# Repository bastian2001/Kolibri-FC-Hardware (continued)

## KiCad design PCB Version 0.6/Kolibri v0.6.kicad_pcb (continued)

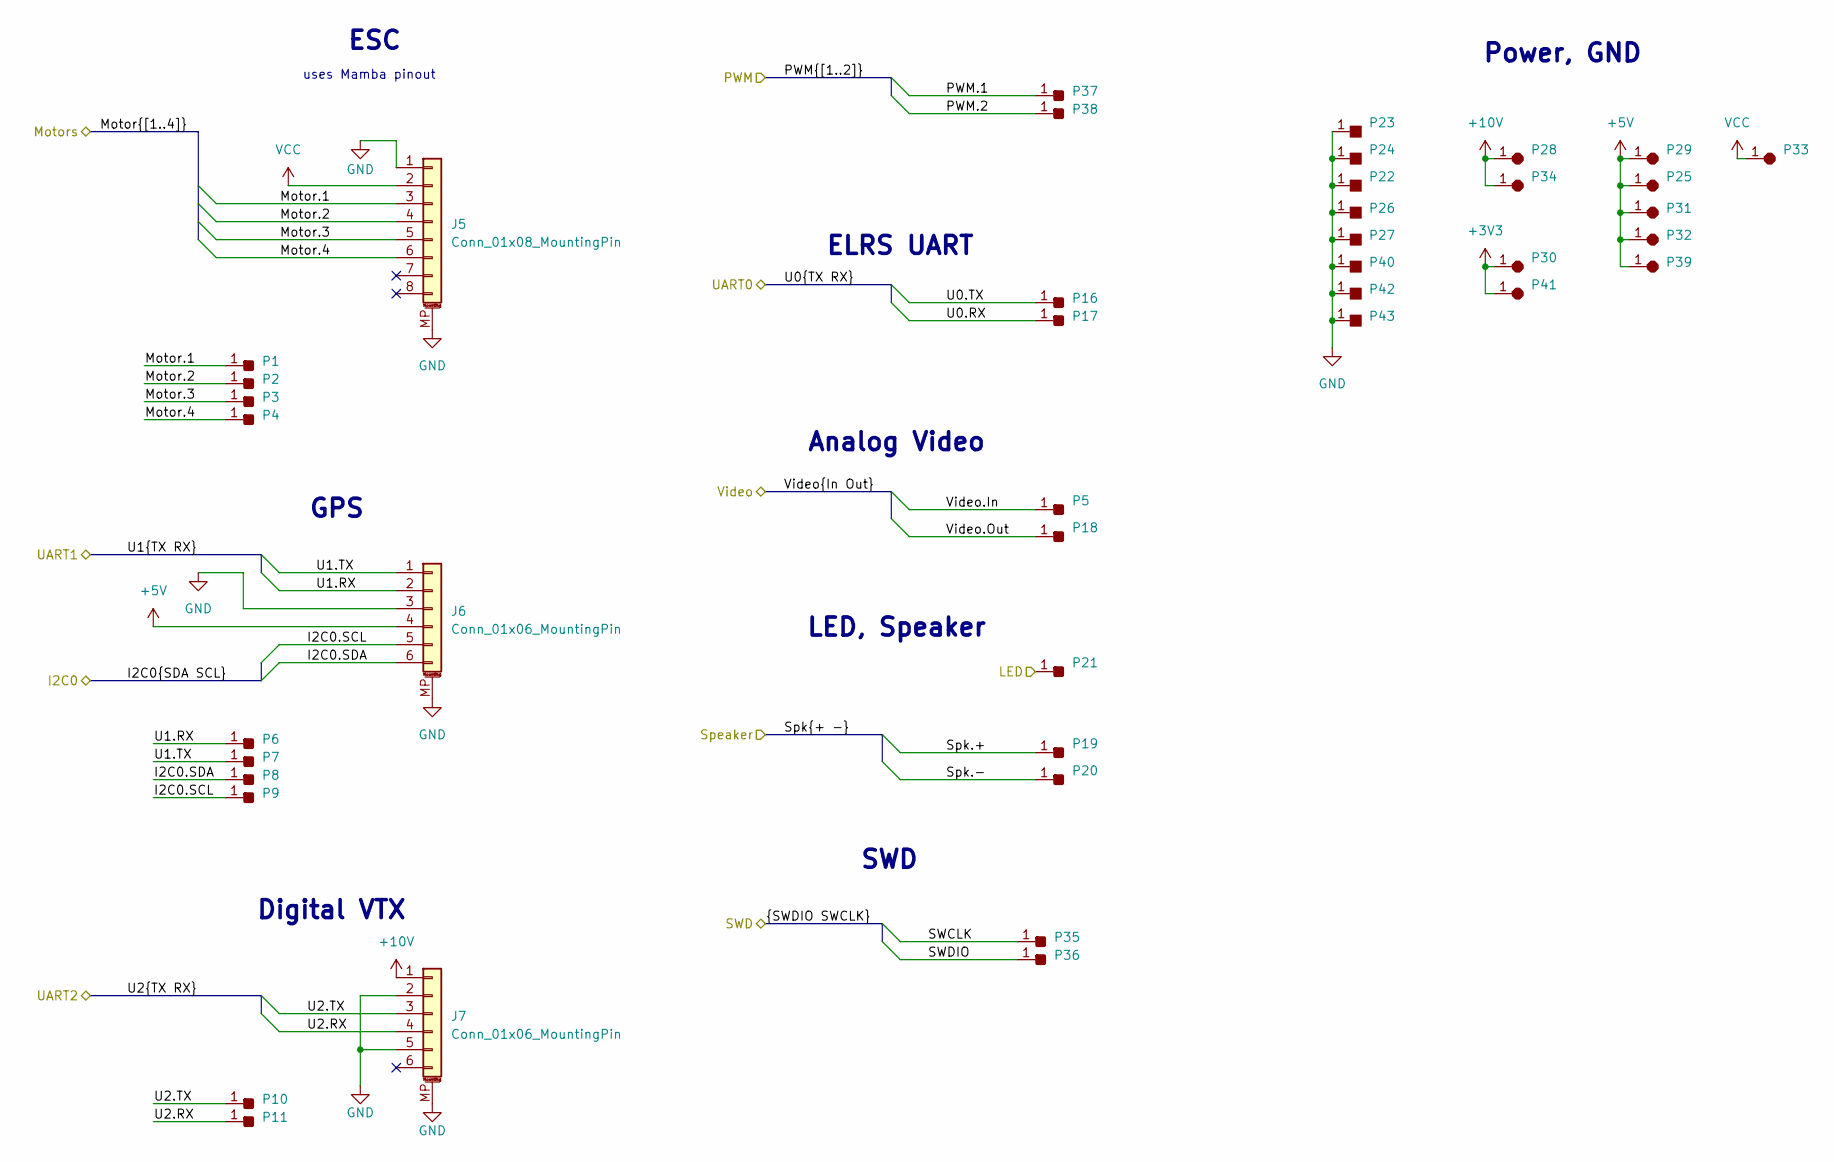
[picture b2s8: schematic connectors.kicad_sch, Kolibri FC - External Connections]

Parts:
J5: Conn_01x08_MountingPin; JST_SH_SM08B-SRSS-TB_1x08-1MP_P1.00mm_Horizontal
J6, J7: Conn_01x06_MountingPin; JST_SH_SM06B-SRSS-TB_1x06-1MP_P1.00mm_Horizontal
P1, P2, P3, P4, P5, P6, P7, P8, P9, P10, P11, P16, P17, P18, P19, P20, P21, P35, P36, P37, P38: Solder_Pad_rounded
P22, P23, P24, P26, P27, P40, P42, P43: Solder_Pad_rect
P25, P28, P29, P30, P31, P32, P33, P34, P39, P41: Solder_Pad_octa

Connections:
+3V3: P30.1, P41.1; also elsewhere on the board
+5V: J6.4, P25.1, P29.1, P31.1, P32.1, P39.1; also elsewhere on the board
+10V: J7.1, P28.1, P34.1; also elsewhere on the board
/Connectors/LED: P21.1; also elsewhere on the board
/I2C0.SCL: J6.5, P9.1; also elsewhere on the board
/I2C0.SDA: J6.6, P8.1; also elsewhere on the board
/Motor.1: J5.3, P1.1; also elsewhere on the board
/Motor.2: J5.4, P2.1; also elsewhere on the board
/Motor.3: J5.5, P3.1; also elsewhere on the board
/Motor.4: J5.6, P4.1; also elsewhere on the board
/PWM.1: P38.1; also elsewhere on the board
/PWM.2: P37.1; also elsewhere on the board
/SWCLK: P35.1; also elsewhere on the board
/SWDIO: P36.1; also elsewhere on the board
/Spk.+: P19.1; also elsewhere on the board
/Spk.-: P20.1; also elsewhere on the board
/U0.RX: P17.1; also elsewhere on the board
/U0.TX: P16.1; also elsewhere on the board
/U1.RX: J6.2, P6.1; also elsewhere on the board
/U1.TX: J6.1, P7.1; also elsewhere on the board
/U2.RX: J7.4, P11.1; also elsewhere on the board
/U2.TX: J7.3, P10.1; also elsewhere on the board
/Video.In: P5.1; also elsewhere on the board
/Video.Out: P18.1; also elsewhere on the board
GND: J5.1, J5.MP (MountPin), J6.3, J6.MP (MountPin), J7.2, J7.5, J7.MP (MountPin), P22.1, P23.1, P24.1, P26.1, P27.1, P40.1, P42.1, P43.1; also elsewhere on the board
VCC: J5.2, P33.1; also elsewhere on the board

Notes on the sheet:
Power, GND
GPS
LED, Speaker
SWD
Analog Video
ESC
uses Mamba pinout
Digital VTX
ELRS UART

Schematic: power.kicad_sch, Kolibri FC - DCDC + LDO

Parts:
C31, C88: 10u; C_0402_1005Metric
C63, C64, C81, C83, C84: 1u; C_0402_1005Metric
C65, C67, C70, C71: 100n; C_0402_1005Metric
C66: 47u; C_1206_3216Metric
C68, C69: 4.7u; C_0805_2012Metric
C72: 22u; C_0805_2012Metric
D10, D13: 1N4148WS; D_SOD-323
IC5, IC6: LMR38025SDRRR; SON50P300X300X80-13N; Mouser Part Number 595-LMR38025SDRRR
L7, L8: 4.7u; L_Cenker_CKCS4020
R10, R16, R20: 10k; R_0402_1005Metric
R13: 100k; R_0402_1005Metric
R14: 39k; R_0402_1005Metric
R15: 40.2k; R_0402_1005Metric
R17: 22.6k; R_0402_1005Metric
R18: 21.5k; R_0402_1005Metric
R19: 90.9k; R_0402_1005Metric
U2: C5250982; SOT-23
U4: TPS2116DRL; SOT-583-8
U7: TPS746-3.3DRV; WSON-6-1EP_2x2mm_P0.65mm_EP1x1.6mm

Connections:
+1V8: C88.1, U2.2 (VO); also elsewhere on the board
+3V3: C31.1, C84.1, R10.2, U7.1 (OUT); also elsewhere on the board
+4V5: D10.1 (K); also elsewhere on the board
+5V: C63.2, C64.2, C81.1, C83.1, D10.2 (A), D13.1 (K), U2.3 (VI), U4.2 (VOUT), U4.7 (VOUT), U7.4 (EN), U7.6 (IN); also elsewhere on the board
+5V_BUCK: C66.1, D13.2 (A), L7.2, R13.1, R15.1, U4.3 (VIN1), U4.5 (MODE)
+5V_USB: U4.6 (VIN2); also elsewhere on the board
+10V: C72.1, L8.2, R19.1; also elsewhere on the board
/Power/DCDC_EN: IC6.3 (EN), R10.1; also elsewhere on the board
GND: C31.2, C63.1, C64.1, C66.2, C67.2, C68.2, C69.2, C70.2, C72.2, C81.2, C83.2, C84.2, C88.2, IC5.1 (GND_1), IC5.2 (GND_2), IC5.13 (EPAD), IC6.1 (GND_1), IC6.2 (GND_2), IC6.13 (EPAD), R14.2, R16.2, R17.2, R18.2, R20.2, U2.1 (GND), U4.1 (GND), U7.3 (GND), U7.5 (PG), U7.7 (EP); also elsewhere on the board
unnamed: C65.1, IC5.10 (BOOT)
unnamed: IC5.8 (FB), R15.2, R16.1
unnamed: IC5.7 (RT/SYNC), R17.1
unnamed: C65.2, IC5.11 (SW_1), IC5.12 (SW_2), L7.1
unnamed: C71.1, IC6.10 (BOOT)
unnamed: IC6.8 (FB), R19.2, R20.1
unnamed: IC6.7 (RT/SYNC), R18.1
unnamed: C71.2, IC6.11 (SW_1), IC6.12 (SW_2), L8.1
unnamed: R13.2, R14.1, U4.4 (PR1)
VCC: C67.1, C68.1, C69.1, C70.1, IC5.3 (EN), IC5.5 (VIN_1), IC5.6 (VIN_2), IC6.5 (VIN_1), IC6.6 (VIN_2); also elsewhere on the board

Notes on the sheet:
12-45V -> 10V 2.5A (6.8uH inductor recommended, but this works)
3.3V 1A LDO
Used for the first RGB LED in each strip, not broken out.
12-45V -> 5V 2.5A
1.8V 300mA LDO (Gyro)
4.2V Supply
5V SMPS
5V Power MUX
10V SMPS
Switches up to 4A (TPS2117) from +5V_USB or +5V_BUCK to +5V. Prefers buck over USB, threshold voltage is about 3.5V. The threshold voltage is low to prevent accidental switchover to USB during peak consumption (worst case in flight). Emergency diode for if that happens during flight.

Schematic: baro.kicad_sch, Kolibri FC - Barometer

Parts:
C23, C24: 100n; C_0402_1005Metric
U11: LPS22HB; ST_HLGA-10_2x2mm_P0.5mm_LayoutBorder3x2y

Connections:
+3V3: C23.1, C24.1, U11.1 (Vdd_IO), U11.5 (SA0), U11.6 (~CS), U11.10 (VDD); also elsewhere on the board
/I2C0.SCL: U11.2 (SCL); also elsewhere on the board
/I2C0.SDA: U11.4 (SDA); also elsewhere on the board
GND: C23.2, C24.2, U11.3 (GND), U11.8 (GND), U11.9 (GND); also elsewhere on the board

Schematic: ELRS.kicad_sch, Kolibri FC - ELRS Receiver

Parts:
C25, C42, C43: 10n; C_0402_1005Metric
C26, C29, C33, C35: 1u; C_0402_1005Metric
C27, C28, C34, C40, C44, C45: 100n; C_0402_1005Metric
C32, C37: 1.5p; C_0402_1005Metric
C36: 10u; C_0402_1005Metric
C38, C39: 15p; C_0402_1005Metric
C41: 470n; C_0402_1005Metric
D11: WS2812B_1615
FL1: 2450FM07D0034T; Mouser Part Number 609-2450FM07D0034T
IC1: SX1280IMLTRT; QFN50P400X400X100-25N-D; Mouser Part Number 947-SX1280IMLTRT
J3: Conn_Coaxial_Small; U.FL_Molex_MCRF_73412-0110_Vertical
L2: 2.0n; L_0402_1005Metric
L3: 3.0n; L_0402_1005Metric
L4: 24n; L_0402_1005Metric
L5: 15u; L_0805_2012Metric
R9: 10k; R_0402_1005Metric
SW2: Button C530669 wo holes
U3: ESP32-C3; QFN-32-1EP_5x5mm_P0.5mm_EP3.7x3.7mm
Y2, Y5: Crystal_GND24; Crystal_SMD_2016-4Pin_2.0x1.6mm

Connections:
+3V3: C25.1, C26.1, C27.1, C28.1, C29.1, C34.1, C36.1, C44.1, C45.1, IC1.11 (VBAT_IO), IC1.15 (VBAT), L2.1, R9.1, U3.11 (VDD3P3_RTC), U3.17 (VDD3P3_CPU), U3.18 (VDD_SPI), U3.31 (VDDA), U3.32 (VDDA); also elsewhere on the board
+4V5: C40.1, D11.2 (VDD); also elsewhere on the board
/ELRS/ELRS_BUTTON: SW2.2, U3.15 (GPIO9)
/ELRS/ELRS_LED_RGB: D11.4 (DIN), U3.14 (GPIO8)
/ELRS/GPIO0: U3.4 (XTAL_32K_P)
/ELRS/GPIO19: U3.26 (GPIO19)
/ELRS/RADIO_BUSY: IC1.7 (BUSY), U3.8 (GPIO3)
/ELRS/RADIO_DIO1: IC1.8 (DIO1), U3.5 (XTAL_32K_N)
/ELRS/RADIO_MISO: IC1.16 (MISO_TX), U3.10 (MTDI)
/ELRS/RADIO_MOSI: IC1.17 (MOSI_RX), U3.9 (MTMS)
/ELRS/RADIO_NSS: IC1.19 (NSS_CTS), U3.13 (MTDO)
/ELRS/RADIO_RST: IC1.3 (NRESET), U3.6 (GPIO2)
/ELRS/RADIO_SCK: IC1.18 (SCK_RTSN), U3.12 (MTCK)
/ELRS/WIFI_ANTENNA: C32.1, L3.2
/PWM.1: U3.16 (GPIO10); also elsewhere on the board
/PWM.2: U3.25 (GPIO18); also elsewhere on the board
/U0.RX: U3.28 (U0TXD); also elsewhere on the board
/U0.TX: U3.27 (U0RXD); also elsewhere on the board
GND: C25.2, C26.2, C27.2, C28.2, C29.2, C32.2, C33.2, C34.2, C35.2, C36.2, C37.2, C38.1, C39.1, C40.2, C41.1, C42.1, C43.2, C44.2, C45.2, D11.3 (GND), FL1.2 (GND_1), FL1.4 (GND_2), IC1.5 (GND_1), IC1.13 (GND_2), IC1.20 (GND_3), IC1.21 (GND_4), IC1.23 (GND_5), IC1.24 (GND_6), IC1.25 (EP), J3.2 (Ext), SW2.1, SW2.3 (MP), SW2.4 (MP), U3.33 (GND), Y2.2, Y2.4, Y5.2, Y5.4; also elsewhere on the board
unnamed: C33.1, L2.2, U3.2 (VDD3P3), U3.3 (VDD3P3)
unnamed: C39.2, L4.1, Y2.1
unnamed: FL1.1 (IN), IC1.22 (RFIO)
unnamed: FL1.3 (OUT), J3.1 (In)
unnamed: C41.2, C42.2, IC1.2 (VDD_IN), IC1.12 (DCC_FB), L5.1
unnamed: IC1.14 (DCC_SW), L5.2
unnamed: C43.1, IC1.1 (VR_PA)
unnamed: IC1.4 (XTA), Y5.3
unnamed: IC1.6 (XTB), Y5.1
unnamed: C35.1, R9.2, U3.7 (CHIP_EN)
unnamed: C37.1, L3.1, U3.1 (LNA_IN)
unnamed: C38.2, U3.29 (XTAL_N), Y2.3
unnamed: L4.2, U3.30 (XTAL_P)

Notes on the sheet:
GPIO1
GPIO6
C37635335
GPIO7
GPIO5
GPIO0
GPIO4
1u for VDD_SPI
9pF load capacitance, C38 + C39 = 7.5pF, and some stray capacitance

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
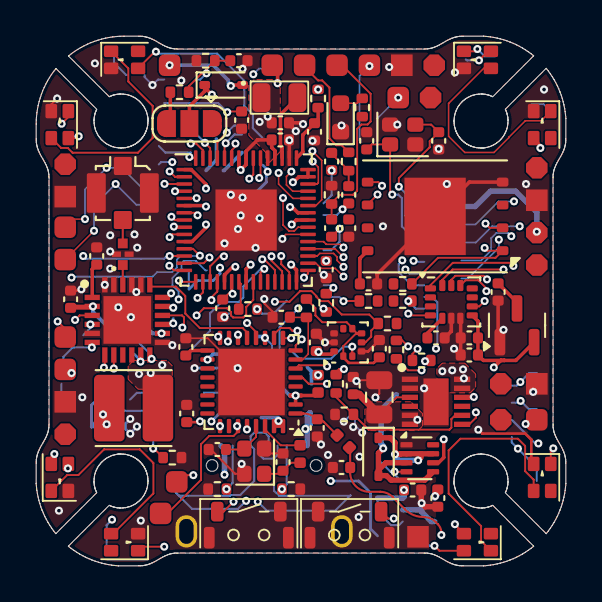
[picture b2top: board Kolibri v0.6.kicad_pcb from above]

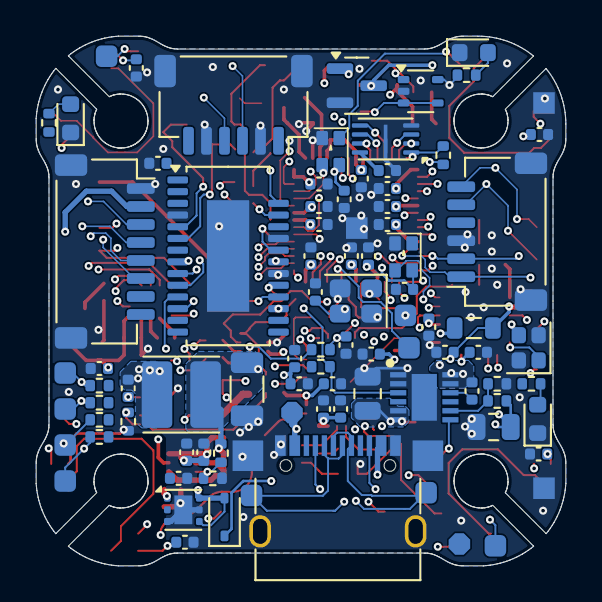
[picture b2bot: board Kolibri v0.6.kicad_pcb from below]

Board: 8 copper layers, 29.4 x 29.4 mm, 201 parts (88 on the bottom side), 121 nets.

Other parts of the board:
C46: 100n; C_0402_1005Metric
D12: 1N4148WS; D_SOD-323
JP1: SolderJumper_3_Open; SolderJumper-3_P1.3mm_Open_RoundedPad1.0x1.5mm
Q1: BSS138; SOT-23

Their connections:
+3V3: C46.1; also elsewhere on the board
+10V: JP1.1 (A); also elsewhere on the board
/RP2350/Speaker: Q1.1 (G); also elsewhere on the board
/Spk.+: D12.1 (K), JP1.2 (C); also elsewhere on the board
/Spk.-: D12.2 (A), Q1.3 (D); also elsewhere on the board
GND: C46.2, Q1.2 (S); also elsewhere on the board
VCC: JP1.3 (B); also elsewhere on the board

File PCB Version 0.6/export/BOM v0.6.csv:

#;Reference;Value;Footprint;Qty;LCSC #;;
1;C1,C3,C4,C5,C6,C7,C8,C9,C10,C16,C17,C18,C19,C20,C21,C23,C24,C27,C28,C30,C34,C40,C44,C45,C46,C48,C56,C65,C67,C70,C71,C76,C85,C86;100n;Capacitor_SMD:C_0402_1005Metric;34;generic;;
2;C2,C11,C12,C13;4.7u;Capacitor_SMD:C_0402_1005Metric;4;generic;;
3;C14,C15,C38,C39,C79,C80;15p;Capacitor_SMD:C_0402_1005Metric;6;generic NP0;;
4;C22;2.2u;Capacitor_SMD:C_0402_1005Metric;1;generic;;
5;C25,C42,C43,C87;10n;Capacitor_SMD:C_0402_1005Metric;4;generic;;
6;C26,C29,C33,C35,C63,C64,C73,C81,C83,C84;1u;Capacitor_SMD:C_0402_1005Metric;10;generic;;
7;C31,C36,C77,C78,C88;10u;Capacitor_SMD:C_0402_1005Metric;5;generic;;
8;C32,C37;1.5p;Capacitor_SMD:C_0402_1005Metric;2;generic NP0;;
9;C41;470n;Capacitor_SMD:C_0402_1005Metric;1;generic;;
10;C66;47u;Capacitor_SMD:C_1206_3216Metric;1;generic 10V+;;
11;C68,C69;4.7u;Capacitor_SMD:C_0805_2012Metric;2;generic 50V+;;
12;C72;22u;Capacitor_SMD:C_0805_2012Metric;1;generic 25V+;;
13;D1,D2,D3,D4,D5,D6,D7,D8,D9,D11;~;Kolibri custom:WS2812B_1615;10;generic;;
14;D10,D12,D13;1N4148WS;Diode_SMD:D_SOD-323;3;generic;;
15;D14;red;LED_SMD:LED_0603_1608Metric;1;generic;;
16;D15;violet;LED_SMD:LED_0603_1608Metric;1;generic;;
17;D16;blue;LED_SMD:LED_0603_1608Metric;1;generic;;
18;D17;green;LED_SMD:LED_0603_1608Metric;1;generic;;
19;FL1;2450FM07D0034T;SamacSys_Parts:2450FM07D0034T;1;C2917726, C6054595, C2651081;;
20;IC1;SX1280IMLTRT;SamacSys_Parts:QFN50P400X400X100-25N-D;1;C2151551;;
21;IC5,IC6;LMR38025SDRRR;SamacSys_Parts:SON50P300X300X80-13N;2;C22405313;;
22;J1;USB_C_Receptacle_USB2.0_16P;Kolibri custom:USB-C SMD+THT;1;C963217;;
23;J3;Conn_Coaxial_Small;Connector_Coaxial:U.FL_Molex_MCRF_73412-0110_Vertical;1;C5137195;;
24;J5;Conn_01x08_MountingPin;Connector_JST:JST_SH_SM08B-SRSS-TB_1x08-1MP_P1.00mm_Horizontal;1;generic, e.g. C7433429;;
25;J6,J7;Conn_01x06_MountingPin;Connector_JST:JST_SH_SM06B-SRSS-TB_1x06-1MP_P1.00mm_Horizontal;2;generic, e.g. C2688763;;
26;L1;3.3u;Kolibri custom:Abracon AOTA 0806;1;C42411119;;
27;L2;2.0n;Inductor_SMD:L_0402_1005Metric;1;generic for RF;;
28;L3;3.0n;Inductor_SMD:L_0402_1005Metric;1;generic for RF;;
29;L4;24n;Inductor_SMD:L_0402_1005Metric;1;generic;;
30;L5;15u;Inductor_SMD:L_0805_2012Metric;1;generic;;
31;L7,L8;4.7u;Inductor_SMD:L_Cenker_CKCS4020;2;generic, e.g. C520275;;
32;P1,P2,P3,P4,P5,P6,P7,P8,P9,P10,P11,P12,P13,P16,P17,P18,P19,P20,P21,P35,P36,P37,P38;~;Kolibri custom:Solder_Pad_rounded;23;-;;
33;P14,P22,P23,P24,P26,P27,P40,P42,P43;~;Kolibri custom:Solder_Pad_rect;9;-;;
34;P15,P25,P28,P29,P30,P31,P32,P33,P34,P39,P41;~;Kolibri custom:Solder_Pad_octa;11;-;;
35;Q1;BSS138;Package_TO_SOT_SMD:SOT-23;1;generic 1%;;
36;R1,R2;27;Resistor_SMD:R_0402_1005Metric;2;generic 1%;;
37;R3;33;Resistor_SMD:R_0402_1005Metric;1;generic 1%;;
38;R4,R21,R22,R23,R30,R33;1k;Resistor_SMD:R_0402_1005Metric;6;generic 1%;;
39;R5,R6;5.1k;Resistor_SMD:R_0402_1005Metric;2;generic 1%;;
40;R7,R8,R34,R35,R36,R37;6.8k;Resistor_SMD:R_0402_1005Metric;6;generic 1%;;
41;R9,R10,R16,R20,R27;10k;Resistor_SMD:R_0402_1005Metric;5;generic 1%;;
42;R13,R26;100k;Resistor_SMD:R_0402_1005Metric;2;generic 1%;;
43;R14;39k;Resistor_SMD:R_0402_1005Metric;1;generic 1%;;
44;R15;40.2k;Resistor_SMD:R_0402_1005Metric;1;generic 1%;;
45;R17;22.6k;Resistor_SMD:R_0402_1005Metric;1;generic 1%;;
46;R18;21.5k;Resistor_SMD:R_0402_1005Metric;1;generic 1%;;
47;R19;90.9k;Resistor_SMD:R_0402_1005Metric;1;generic 1%;;
48;R24,R25;75;Resistor_SMD:R_0402_1005Metric;2;generic 1%;;
49;R28;8.2k;Resistor_SMD:R_0402_1005Metric;1;generic 1%;;
50;R29;3.3k;Resistor_SMD:R_0402_1005Metric;1;generic 1%;;
51;R31;2.2k;Resistor_SMD:R_0402_1005Metric;1;generic 1%;;
52;R41;22k;Resistor_SMD:R_0402_1005Metric;1;generic 1%;;
53;SW1,SW2;~;Kolibri custom:Button C530669 wo holes;2;generic, e.g. C530669;;
54;U1;RP2350A;Kolibri custom:QFN-60_EP_7x7_Pitch0.4mm;1;C42411118;;
55;U2;C5250982;Package_TO_SOT_SMD:SOT-23;1;Generic 1.8V, 70dB, e.g. C5250982;;
56;U3;ESP8685-H4;Package_DFN_QFN:QFN-28-1EP_4x4mm_P0.4mm_EP2.4x2.4mm;1;C4944062;;
57;U4;TPS2116DRL;Package_TO_SOT_SMD:SOT-583-8;1;C22399676, C3235557;;
58;U5;AT7456E;Package_SO:HTSSOP-28-1EP_4.4x9.7mm_P0.65mm_EP2.75x6.2mm;1;C82351;;
59;U6;MT29F2G01ABAGDWB-IT:G;Package_SON:WSON-8-1EP_8x6mm_P1.27mm_EP3.4x4.3mm;1;C410863;;
60;U7;TPS746-3.3DRV;Package_SON:WSON-6-1EP_2x2mm_P0.65mm_EP1x1.6mm;1;C2846784;;
61;U8;C3029047;Package_TO_SOT_SMD:SOT-353_SC-70-5;1;generic LMV321. e.g. C3029047;;
62;U10;W25Q16JVUXIQ;Package_SON:Winbond_USON-8-1EP_3x2mm_P0.5mm_EP0.2x1.6mm;1;C2843335;;alternatively, dnp and use RP2354
63;U11;LPS22HB;Package_LGA:ST_HLGA-10_2x2mm_P0.5mm_LayoutBorder3x2y;1;C94049;;
64;U12;ICM-42688-P;Package_LGA:LGA-14_3x2.5mm_P0.5mm_LayoutBorder3x4y;1;C1850418;;
65;Y1;Crystal_GND24;Crystal:Crystal_SMD_2520-4Pin_2.5x2.0mm;1;generic 12 Mhz, e.g. C7294610;;
66;Y2,Y4,Y5;Crystal_GND24;Crystal:Crystal_SMD_2016-4Pin_2.0x1.6mm;3;generic, 27MHz e.g. C18214311, 52MHz e.g. C3034316, 40MHz e.g.C37635335;;

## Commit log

2025-09-27 reordering
2025-09-27 PCB v0.2, not done yet
    still missing: Vias are untented, remove 0R resistors for voltage rails after v0.1 testing
2025-09-27 Schematics PDF and solder rig for the stencil
2025-09-27 some PCB v0.2 improvements
2025-09-27 added pictures of board
2025-09-27 updated changelog for PCB revisions
2025-09-27 updated changelog
2025-09-27 v0.2 PCB ordered
2025-09-27 moved simulations to "other"
2025-09-27 first works on v0.3 pcb
2025-09-27 PCB v0.3 wip - 0 rule violations, but not happy with routing
2025-09-27 PCB version 0.3, see Cangelog.md
2025-09-27 Started library of external documentation
2025-09-27 update changelog
2025-09-27 V0.4 PCB
    hopefully fixes all the V0.3 issues:
    - ELRS range --> better grounding, RFX2401C
    - ELRS WiFi --> filter in front of antenna
    - ELRS crystal
    - ELRS boot button
    - I2C Pullups
2025-09-27 v0.4 as ordered, incl. exports (PDF, Gerber, BOM)
2025-09-27 move solder rig where it belongs
2025-09-27 Update voltage divider for power mux
    fixes 3.3V voltage drops due to the power switch switching too late after removing battery / too early when attaching battery
2025-09-27 add standalone ELRS RX (as ordered)
2025-09-27 PCB version 0.5 (#56)
2025-09-27 Create LICENSE
2025-09-27 move deprecated pcbs to deprecated
2025-09-30 started work on 20mm FC
    Changes so far (schematics only):
    - ELRS from TD with PA/LNA to single without PA/LNA
    - ELRS from normal ESP32 to ESP32-C3
    - Gyro from BMI270 to ICM-42688-P with external clock
    - Blackbox from SD slot to 2GBit flash chip
    - left it at RP2350A: 2354 unavailable and 2350B too large (and barely not needed)
2025-09-30 replace USB JST with pads and remove USB TVS
2025-09-30 remove current sensor ADC, swap opamp, add dcdc switch
2025-09-30 switch crystal footprints
2025-10-01 WIP layout
2025-10-01 layout first draft done
2025-10-05 wip routing
2025-10-06 0 DRC errors
    TODO:
    - impedance matching
    - silkscreen
2025-10-06 ESP8685
2025-10-06 impedance matching, labels
2025-10-07 finished PCB
2025-10-07 V0.6 as ordered
2025-10-07 PCB Version 0.6 (20mm FC) (#1)
    Changes compared to V0.5
    - ELRS from TD with PA/LNA to single without PA/LNA
    - ELRS from ESP32 to ESP8685 (C3)
    - Gyro from BMI270 to ICM-42688-P with external clock
    - Blackbox from SD slot to 2GBit flash chip
    - left it at RP2350A: 2354 unavailable and 2350B too large (and barely not needed)
2025-10-07 update changelog, readme, add FC images
2025-10-08 start Pixel OSD testboard
2025-10-18 ^wip layout
2025-10-23 layout done?
2025-11-02 0 DRC errors
2025-11-02 upgrade to 6 layers for free POFV and free thinner
2025-11-02 some silkscreen
2025-11-04 as ordered
2025-11-04 Pixel OSD Testboard (#2)
    The goal of this board is to try to draw the OSD with the MCU itself. This would save BOM costs, reduce reliance on the AT7456E, and give more features like tighter OSD lines
2025-11-10 added schematics and BOM for Pixel OSD Testboard
